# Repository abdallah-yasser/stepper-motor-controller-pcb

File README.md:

<div align="center">

# Stepper Motor Controller PCB

**An Arduino-compatible stepper motor controller board: ATmega328P + DRV8825 on a compact 4-layer PCB**

</div>

---

## Table of Contents
- [Overview](#overview)
- [Key Features](#key-features)
- [Specifications](#specifications)
- [Schematic](#schematic)
- [PCB Layout](#pcb-layout)
- [Getting Started](#getting-started)
- [Project Structure](#project-structure)
- [Future Work](#future-work)
- [Author](#author)

## Overview
A single-board solution for driving a bipolar stepper motor. It combines a microcontroller, a USB interface, a stepper driver and power conditioning on one 60 × 47 mm PCB. Because the board is Arduino Uno compatible, it can be programmed from the Arduino IDE over USB. Typical uses include small CNC axes, 3D-printer-style mechanisms, camera sliders and robotic joints.

## Key Features
- **ATmega328P** microcontroller with a 16 MHz crystal, reset button and ISP header for bootloader flashing.
- **DRV8825 stepper driver**:
  - Up to 1/32 microstepping
  - Adjustable current limit through the on-board potentiometer
  - 4-pin motor output terminal
- **USB-to-UART** through a CH340G and a Micro-USB connector, for programming and serial communication.
- **Robust power input**:
  - Screw terminal for the motor supply
  - SS34 Schottky diode for reverse-polarity protection
  - NCP1117 5 V LDO regulator
  - Resettable polyfuse on USB
- **4 filtered analog inputs** on 3-pin headers, each with an RC low-pass filter (1.6 kΩ / 100 nF, fc ≈ 1 kHz) for clean sensor readings.
- **Power and indicator LEDs.**

## Specifications
| Parameter | Value |
|-----------|-------|
| Board size | 60 × 47 mm, rounded corners |
| Layer stack | 4 layers: F.Cu / In1.Cu / In2.Cu / B.Cu |
| Component count | 63 footprints, mostly SMD |
| Microcontroller | ATmega328P-A (TQFP-32) @ 16 MHz |
| Motor driver | TI DRV8825 |
| USB bridge | WCH CH340G |
| Logic supply | 5 V (NCP1117-5.0) |
| EDA tool | KiCad 10 |

## Schematic

The design is organized into clearly separated functional blocks:

| Block | Main components | Function |
|-------|-----------------|----------|
| Stepper motor driver | DRV8825, sense resistors, bulk capacitors | Drives the stepper coils with current regulation |
| Power regulation | NCP1117-5.0, SS34, filter capacitors | Protected 5 V logic rail |
| Microcontroller | ATmega328P-A, 16 MHz crystal, reset, ISP | Control logic |
| USB / UART | CH340G, Micro-USB, polyfuse | Programming and serial link |
| Low-pass filters | 4 × RC networks | Sensor signal conditioning |

## PCB Layout
| Front copper | All layers |
|:---:|:---:|
|  |  |

Layout notes:
- The 4-layer stack-up has copper pour zones on the inner layers (In1.Cu / In2.Cu), with signal routing mainly on the top layer.
- Most components are SMD on the top side, which keeps assembly single-sided.
- The power input, motor terminal, USB and sensor headers are placed along the board edges for easy cabling.

## Getting Started
1. Install [KiCad](https://www.kicad.org/) 10 or newer.
2. Clone the repository:
   ```bash
   git clone https://github.com/abdallahnafady54321-bit/stepper-motor-controller-pcb.git
   ```
3. Open `hardware/stepper_controller.kicad_pro`.
4. The custom **DRV8825** symbol lives in `hardware/my_project_lib.kicad_sym`, and the included `sym-lib-table` links it automatically.

**Manufacturing:** generate Gerber and drill files from the PCB editor (*File → Fabrication Outputs*). The board can be ordered from any standard 4-layer PCB service.

## Project Structure
```
stepper-motor-controller-pcb/
├── hardware/
│   ├── stepper_controller.kicad_pro   # KiCad project
│   ├── stepper_controller.kicad_sch   # Schematic
│   ├── stepper_controller.kicad_pcb   # PCB layout
│   ├── my_project_lib.kicad_sym       # Custom DRV8825 symbol
│   └── sym-lib-table                  # Project symbol library table
└── images/                            # Renders and screenshots
```

## Future Work
- Add jumpers for selecting the microstepping mode and break out the DRV8825 FAULT pin.
- Add limit-switch inputs with optional optical isolation.
- Assemble a prototype and validate it with firmware, for example AccelStepper.

## Author
**Abdallah Yasser**, Mechatronics Engineering
[GitHub](https://github.com/abdallahnafady54321-bit)

## License
This project is licensed under the MIT License. See [LICENSE](LICENSE) for details.

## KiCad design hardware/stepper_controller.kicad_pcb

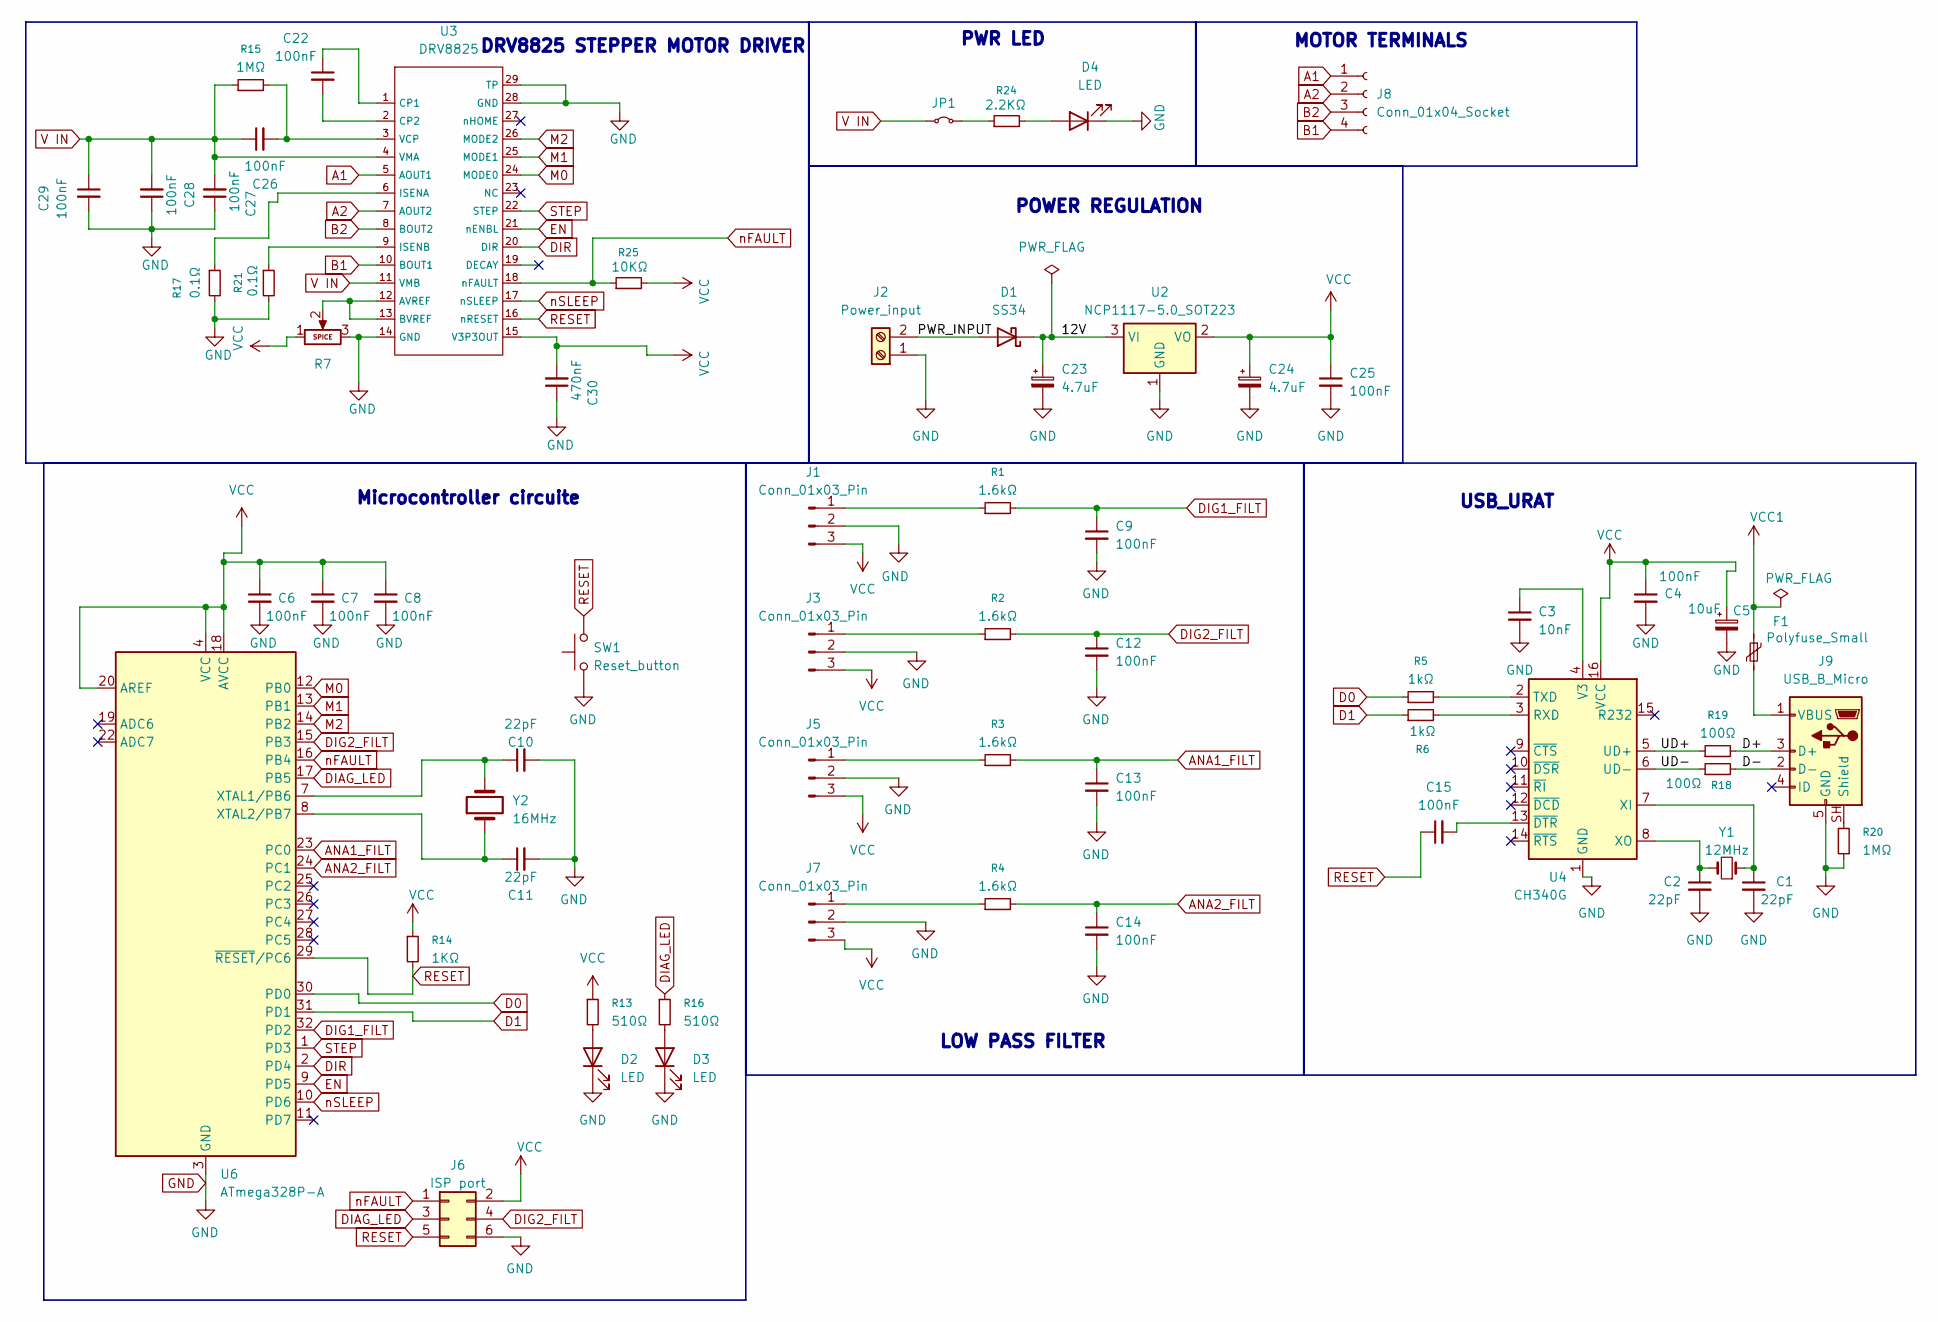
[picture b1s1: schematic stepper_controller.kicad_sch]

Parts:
C1, C2, C10, C11: 22pF; C_0805_2012Metric
C3: 10nF; C_0805_2012Metric
C4, C6, C7, C8, C9, C12, C13, C14, C15, C22, C25, C26, C27, C28, C29: 100nF; C_0805_2012Metric
C5: 10uF; CP_EIA-3216-12_Kemet-S
C23, C24: 4.7uF; CP_EIA-3216-18_Kemet-A
C30: 470nF; C_0805_2012Metric
D1: SS34; D_SMA
D2, D3, D4: LED; LED_1206_3216Metric
F1: Polyfuse_Small; Fuse_1206_3216Metric
J1, J3, J5, J7: Conn_01x03_Pin; PinHeader_1x03_P2.54mm_Vertical
J2: Power_input; TerminalBlock_Phoenix_PT-1,5-2-5.0-H_1x02_P5.00mm_Horizontal
J6: ISP port; PinHeader_2x03_P2.54mm_Vertical
J8: Conn_01x04_Socket; PinHeader_1x04_P2.54mm_Vertical
J9: USB_B_Micro; USB_Micro-B_Molex_47346-0001
JP1: SolderJumper-2_P1.3mm_Bridged_Pad1.0x1.5mm
R1, R2, R3, R4: 1.6kΩ; R_0805_2012Metric
R5, R6: 1kΩ; R_0805_2012Metric
R7: Potentiometer; Potentiometer_Bourns_TC33X_Vertical
R13, R16: 510Ω; R_0805_2012Metric
R14: 1KΩ; R_0805_2012Metric
R15, R20: 1MΩ; R_0805_2012Metric
R17, R21: 0.1Ω; R_0805_2012Metric
R18, R19: 100Ω; R_0805_2012Metric
R24: 2.2KΩ; R_0805_2012Metric
R25: 10KΩ; R_0805_2012Metric
SW1: Reset_button; SW_PUSH_6mm
U2: NCP1117-5.0_SOT223; SOT-223-3_TabPin2
U3: DRV8825; HTSSOP-28-1EP_4.4x9.7mm_P0.65mm_EP3.4x9.5mm_ThermalVias
U4: CH340G; SOIC-16_3.9x9.9mm_P1.27mm
U6: ATmega328P-A; TQFP-32_7x7mm_P0.8mm
Y1: 12MHz; Crystal_SMD_HC49-SD
Y2: 16MHz; Crystal_SMD_HC49-SD

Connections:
/12V: C23.1, D1.1 (K), U2.3 (VI)
/D+: J9.3 (D+), R19.2
/D-: J9.2 (D-), R18.2
/PWR_INPUT: D1.2 (A), J2.2
/UD+: R19.1, U4.5 (UD+)
/UD-: R18.1, U4.6 (UD-)
A1: J8.1, U3.5 (AOUT1)
A2: J8.2, U3.7 (AOUT2)
ANA1_FILT: C13.1, R3.2, U6.23 (PC0)
ANA2_FILT: C14.1, R4.2, U6.24 (PC1)
B1: J8.4, U3.10 (BOUT1)
B2: J8.3, U3.8 (BOUT2)
D0: R5.1, U6.30 (PD0)
D1: R6.1, U6.31 (PD1)
DIAG_LED: J6.3, R16.1, U6.17 (PB5)
DIG1_FILT: C9.1, R1.2, U6.32 (PD2)
DIG2_FILT: C12.1, J6.4, R2.2, U6.15 (PB3)
DIR: U3.20 (DIR), U6.2 (PD4)
EN: U3.21 (nENBL), U6.9 (PD5)
GND: C1.2, C2.2, C3.2, C4.2, C5.2, C6.2, C7.2, C8.2, C9.2, C10.2, C11.2, C12.2, C13.2, C14.2, C23.2, C24.2, C25.2, C27.1, C28.1, C29.2, C30.1, D2.1 (K), D3.1 (K), D4.1 (K), J1.2, J2.1, J3.2, J5.2, J6.6, J7.2, J9.5 (GND), R7.3, R17.2, R20.1, R21.2, SW1.1, U2.1 (GND), U3.14 (GND), U3.28 (GND), U3.29 (TP), U4.1 (GND), U6.3 (GND), U6.5 (GND), U6.21 (GND)
M0: U3.24 (MODE0), U6.12 (PB0)
M1: U3.25 (MODE1), U6.13 (PB1)
M2: U3.26 (MODE2), U6.14 (PB2)
unnamed: D2.2 (A), R13.2
unnamed: D3.2 (A), R16.2
unnamed: D4.2 (A), R24.2
unnamed: J1.1, R1.1
unnamed: J3.1, R2.1
unnamed: J5.1, R3.1
unnamed: J7.1, R4.1
unnamed: J9.SH (Shield), R20.2
unnamed: F1.2, J9.1 (VBUS)
unnamed: JP1.2 (B), R24.1
unnamed: R7.2, U3.12 (AVREF), U3.13 (BVREF)
unnamed: C22.1, U3.1 (CP1)
unnamed: C22.2, U3.2 (CP2)
unnamed: R17.1, U3.6 (ISENA)
unnamed: R21.1, U3.9 (ISENB)
unnamed: C26.2, R15.2, U3.3 (VCP)
unnamed: R6.2, U4.3 (RXD)
unnamed: R5.2, U4.2 (TXD)
unnamed: C3.1, U4.4 (V3)
unnamed: C1.1, U4.7 (XI), Y1.1
unnamed: C2.1, U4.8 (XO), Y1.2
unnamed: C15.2, U4.13 (~DTR)
unnamed: C10.1, U6.7 (XTAL1/PB6), Y2.2
unnamed: C11.1, U6.8 (XTAL2/PB7), Y2.1
RESET: C15.1, J6.5, R14.2, SW1.2, U3.16 (nRESET), U6.29 (~RESET/PC6)
STEP: U3.22 (STEP), U6.1 (PD3)
V IN: C26.1, C27.2, C28.2, C29.1, JP1.1 (A), R15.1, U3.4 (VMA), U3.11 (VMB)
VCC: C4.1, C5.1, C6.1, C7.1, C8.1, C24.1, C25.1, C30.2, J1.3, J3.3, J5.3, J6.2, J7.3, R7.1, R13.1, R14.1, R25.2, U2.2 (VO), U3.15 (V3P3OUT), U4.16 (VCC), U6.4 (VCC), U6.6 (VCC), U6.18 (AVCC), U6.20 (AREF)
VCC1: F1.1
nFAULT: J6.1, R25.1, U3.18 (nFAULT), U6.16 (PB4)
nSLEEP: U3.17 (nSLEEP), U6.10 (PD6)

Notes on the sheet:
DRV8825 STEPPER MOTOR DRIVER
LOW PASS FILTER
MOTOR TERMINALS
USB_URAT
POWER REGULATION
PWR LED
Microcontroller circuite

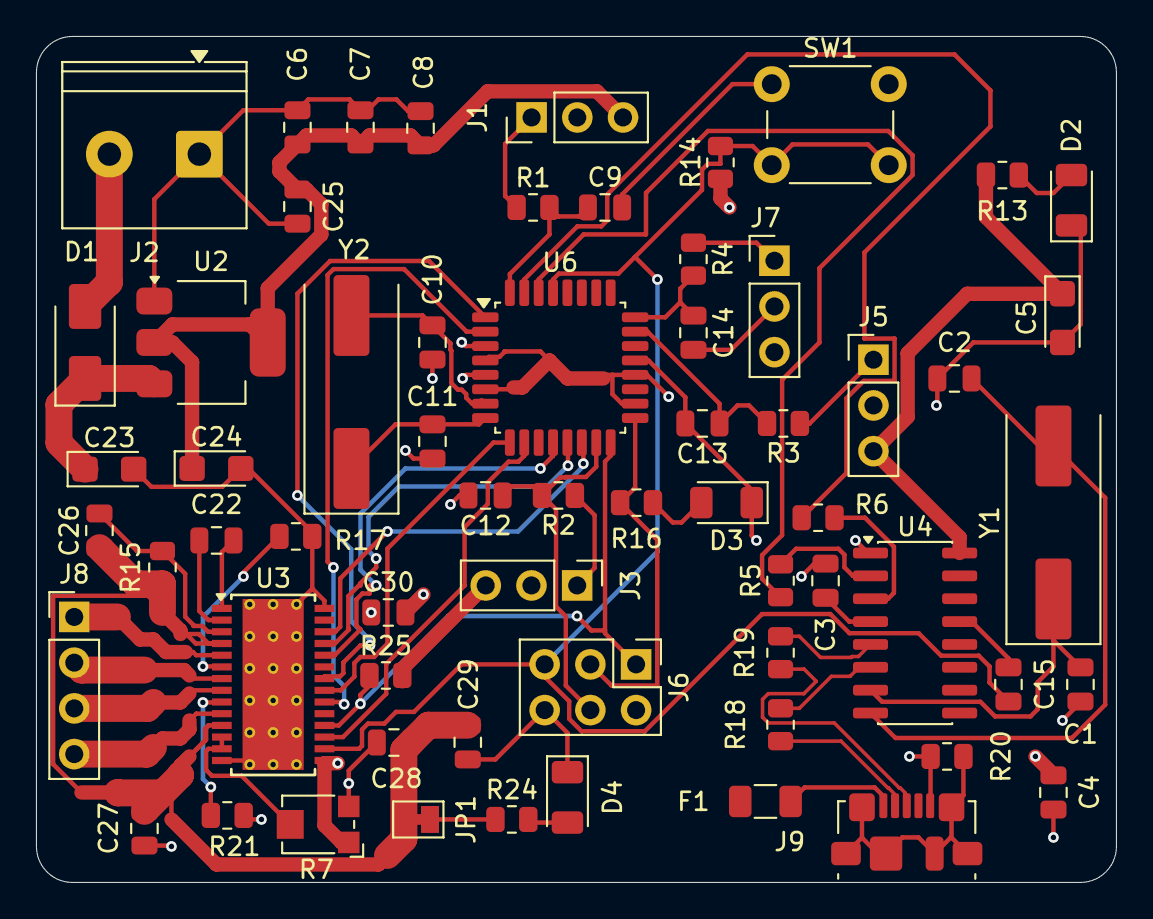
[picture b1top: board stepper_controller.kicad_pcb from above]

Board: 4 copper layers, 60.0 x 47.0 mm, 63 parts (0 on the bottom side), 53 nets.

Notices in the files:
README.md:
License: MIT
